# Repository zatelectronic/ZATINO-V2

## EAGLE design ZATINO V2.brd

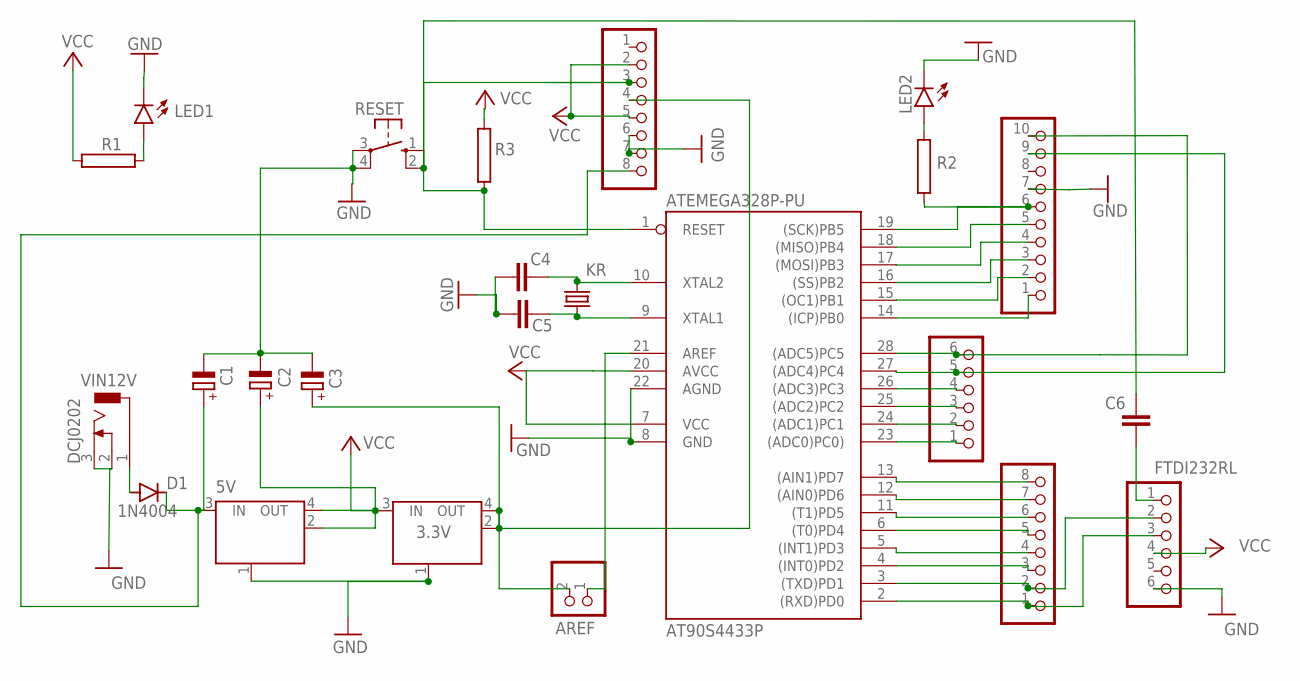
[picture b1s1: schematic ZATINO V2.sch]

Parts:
3.3V, 5V: MC33269ST-3.3T3; SOT223
AD: 6x1F-H8.5; 1X06
ATEMEGA328P-PU: AT90S4433P; DIL28-3
C1, C2, C3: CPOL-EUE2,5-6E; E2,5-6E
C4, C5: C2.5/2; C2.5-2
C6: C2,5-3; C2.5-3
D1: 1N4004; DO41-10
FTDI232RL: PINHD-1X6; 1X06
IOH: 10x1F-H8.5; 1X10
IOL: 8x1F-H8.5; 1X08
JP2: PINHD-1X2; 1X02
KR: CRYSTALHC49U-V; HC49U-V
LED1, LED2: LED5MM
POWER: 8x1F-H8.5; 1X08
R1, R2: RRS1/8; RS1/8
R3: RRS1/4; RS1/4
RESET: 10-XX; B3F-10XX
VIN12V: DCJ0202

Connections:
GND: 3.3V.1 (GND/ADJ), 5V.1 (GND/ADJ), ATEMEGA328P-PU.8 (GND), ATEMEGA328P-PU.22 (AGND), C1.-, C2.-, C3.-, C4.1, C5.1, FTDI232RL.6, IOH.7, LED1.K (C), LED2.K (C), POWER.6, POWER.7, RESET.3, RESET.4 (P1), VIN12V.2, VIN12V.3
unnamed: AD.6, ATEMEGA328P-PU.28 ((ADC5)PC5), IOH.10
unnamed: AD.5, ATEMEGA328P-PU.27 ((ADC4)PC4), IOH.9
unnamed: AD.3, ATEMEGA328P-PU.25 ((ADC2)PC2)
unnamed: AD.4, ATEMEGA328P-PU.26 ((ADC3)PC3)
unnamed: AD.2, ATEMEGA328P-PU.24 ((ADC1)PC1)
unnamed: AD.1, ATEMEGA328P-PU.23 ((ADC0)PC0))
unnamed: ATEMEGA328P-PU.2 ((RXD)PD0), FTDI232RL.3, IOL.1
unnamed: ATEMEGA328P-PU.3 ((TXD)PD1), FTDI232RL.2, IOL.2
unnamed: ATEMEGA328P-PU.4 ((INT0)PD2), IOL.3
unnamed: ATEMEGA328P-PU.5 ((INT1)PD3), IOL.4
unnamed: ATEMEGA328P-PU.6 ((T0)PD4), IOL.5
unnamed: ATEMEGA328P-PU.11 ((T1)PD5), IOL.6
unnamed: ATEMEGA328P-PU.12 ((AIN0)PD6), IOL.7
unnamed: ATEMEGA328P-PU.13 ((AIN1)PD7), IOL.8
unnamed: ATEMEGA328P-PU.14 ((ICP)PB0), IOH.1
unnamed: ATEMEGA328P-PU.15 ((OC1)PB1), IOH.2
unnamed: ATEMEGA328P-PU.16 ((SS)PB2), IOH.3
unnamed: ATEMEGA328P-PU.17 ((MOSI)PB3), IOH.4
unnamed: ATEMEGA328P-PU.18 ((MISO)PB4), IOH.5
unnamed: ATEMEGA328P-PU.19 ((SCK)PB5), IOH.6, R2.1
unnamed: 5V.3 (IN), C1.+, D1.C, POWER.8
unnamed: ATEMEGA328P-PU.10 (XTAL2), C4.2, KR.2
unnamed: ATEMEGA328P-PU.9 (XTAL1), C5.2, KR.1
unnamed: C6.1, FTDI232RL.1
unnamed: 3.3V.2 (OUT), 3.3V.4 (OUT), C3.+, JP2.2, POWER.4
unnamed: D1.A, VIN12V.1
unnamed: LED2.A, R2.2
unnamed: ATEMEGA328P-PU.1 (RESET), C6.2, POWER.3, R3.1, RESET.1 (S), RESET.2 (S1)
unnamed: ATEMEGA328P-PU.21 (AREF), JP2.1
unnamed: LED1.A, R1.2
VCC: 3.3V.3 (IN), 5V.2 (OUT), 5V.4 (OUT), ATEMEGA328P-PU.7 (VCC), ATEMEGA328P-PU.20 (AVCC), C2.+, FTDI232RL.4, POWER.2, POWER.5, R1.1, R3.2

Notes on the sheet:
AREF

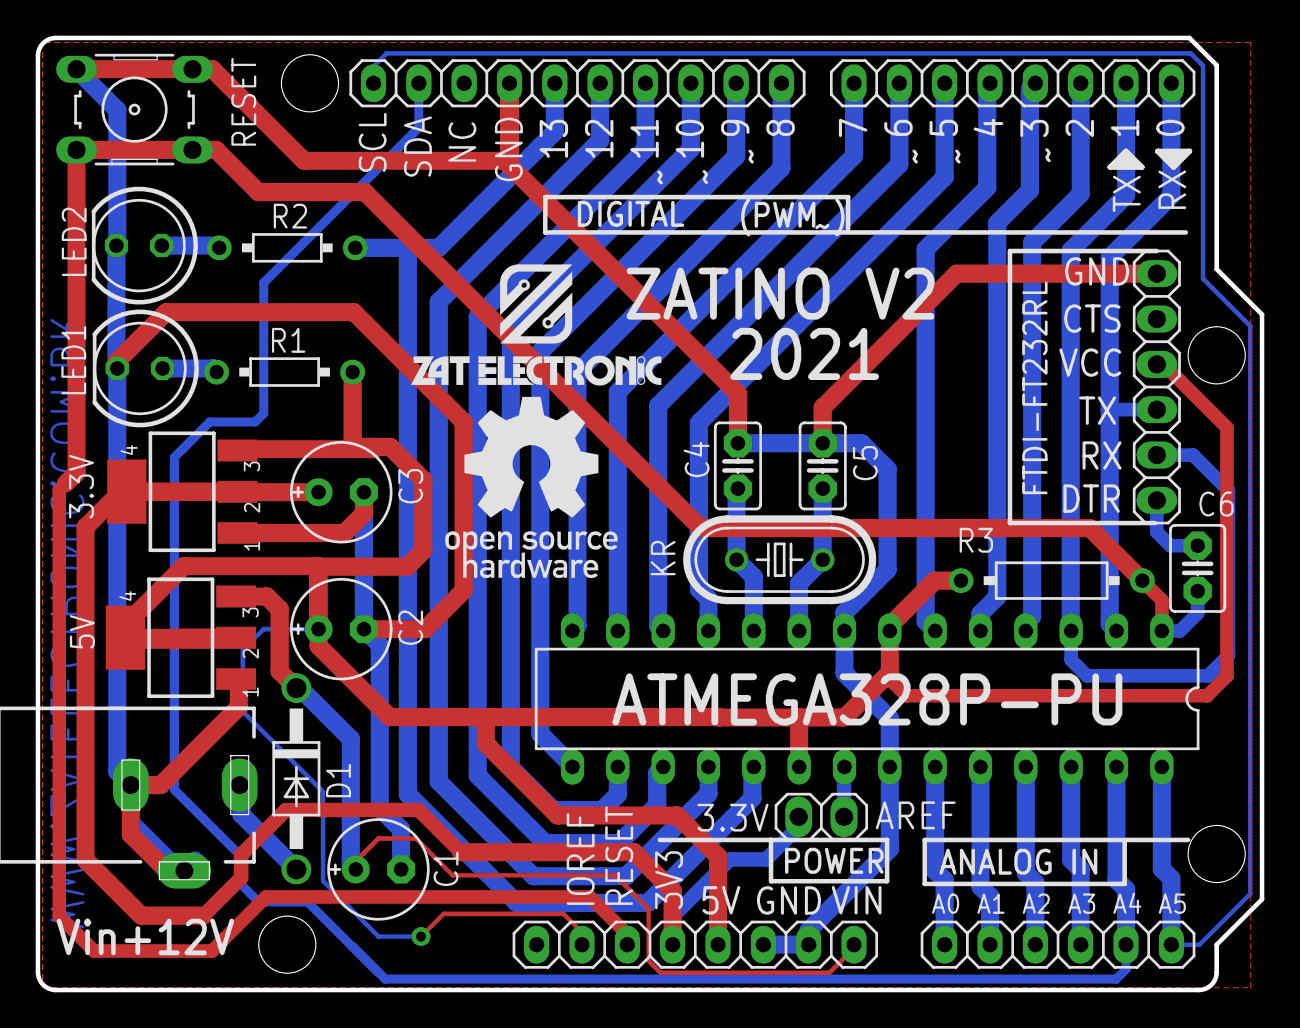
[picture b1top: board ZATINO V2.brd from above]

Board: 2 copper layers, 68.6 x 53.3 mm, 26 parts (0 on the bottom side), 32 nets.

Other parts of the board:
U$1: LOGO_OPENHARDWARE_3
U$3: LOGO_ESCRITA_MEDIO

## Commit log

2021-10-23 PRIMEIRO ENVIO
2021-10-25 ATUALIZAÇÃO
2021-11-27 ENVIO 2
